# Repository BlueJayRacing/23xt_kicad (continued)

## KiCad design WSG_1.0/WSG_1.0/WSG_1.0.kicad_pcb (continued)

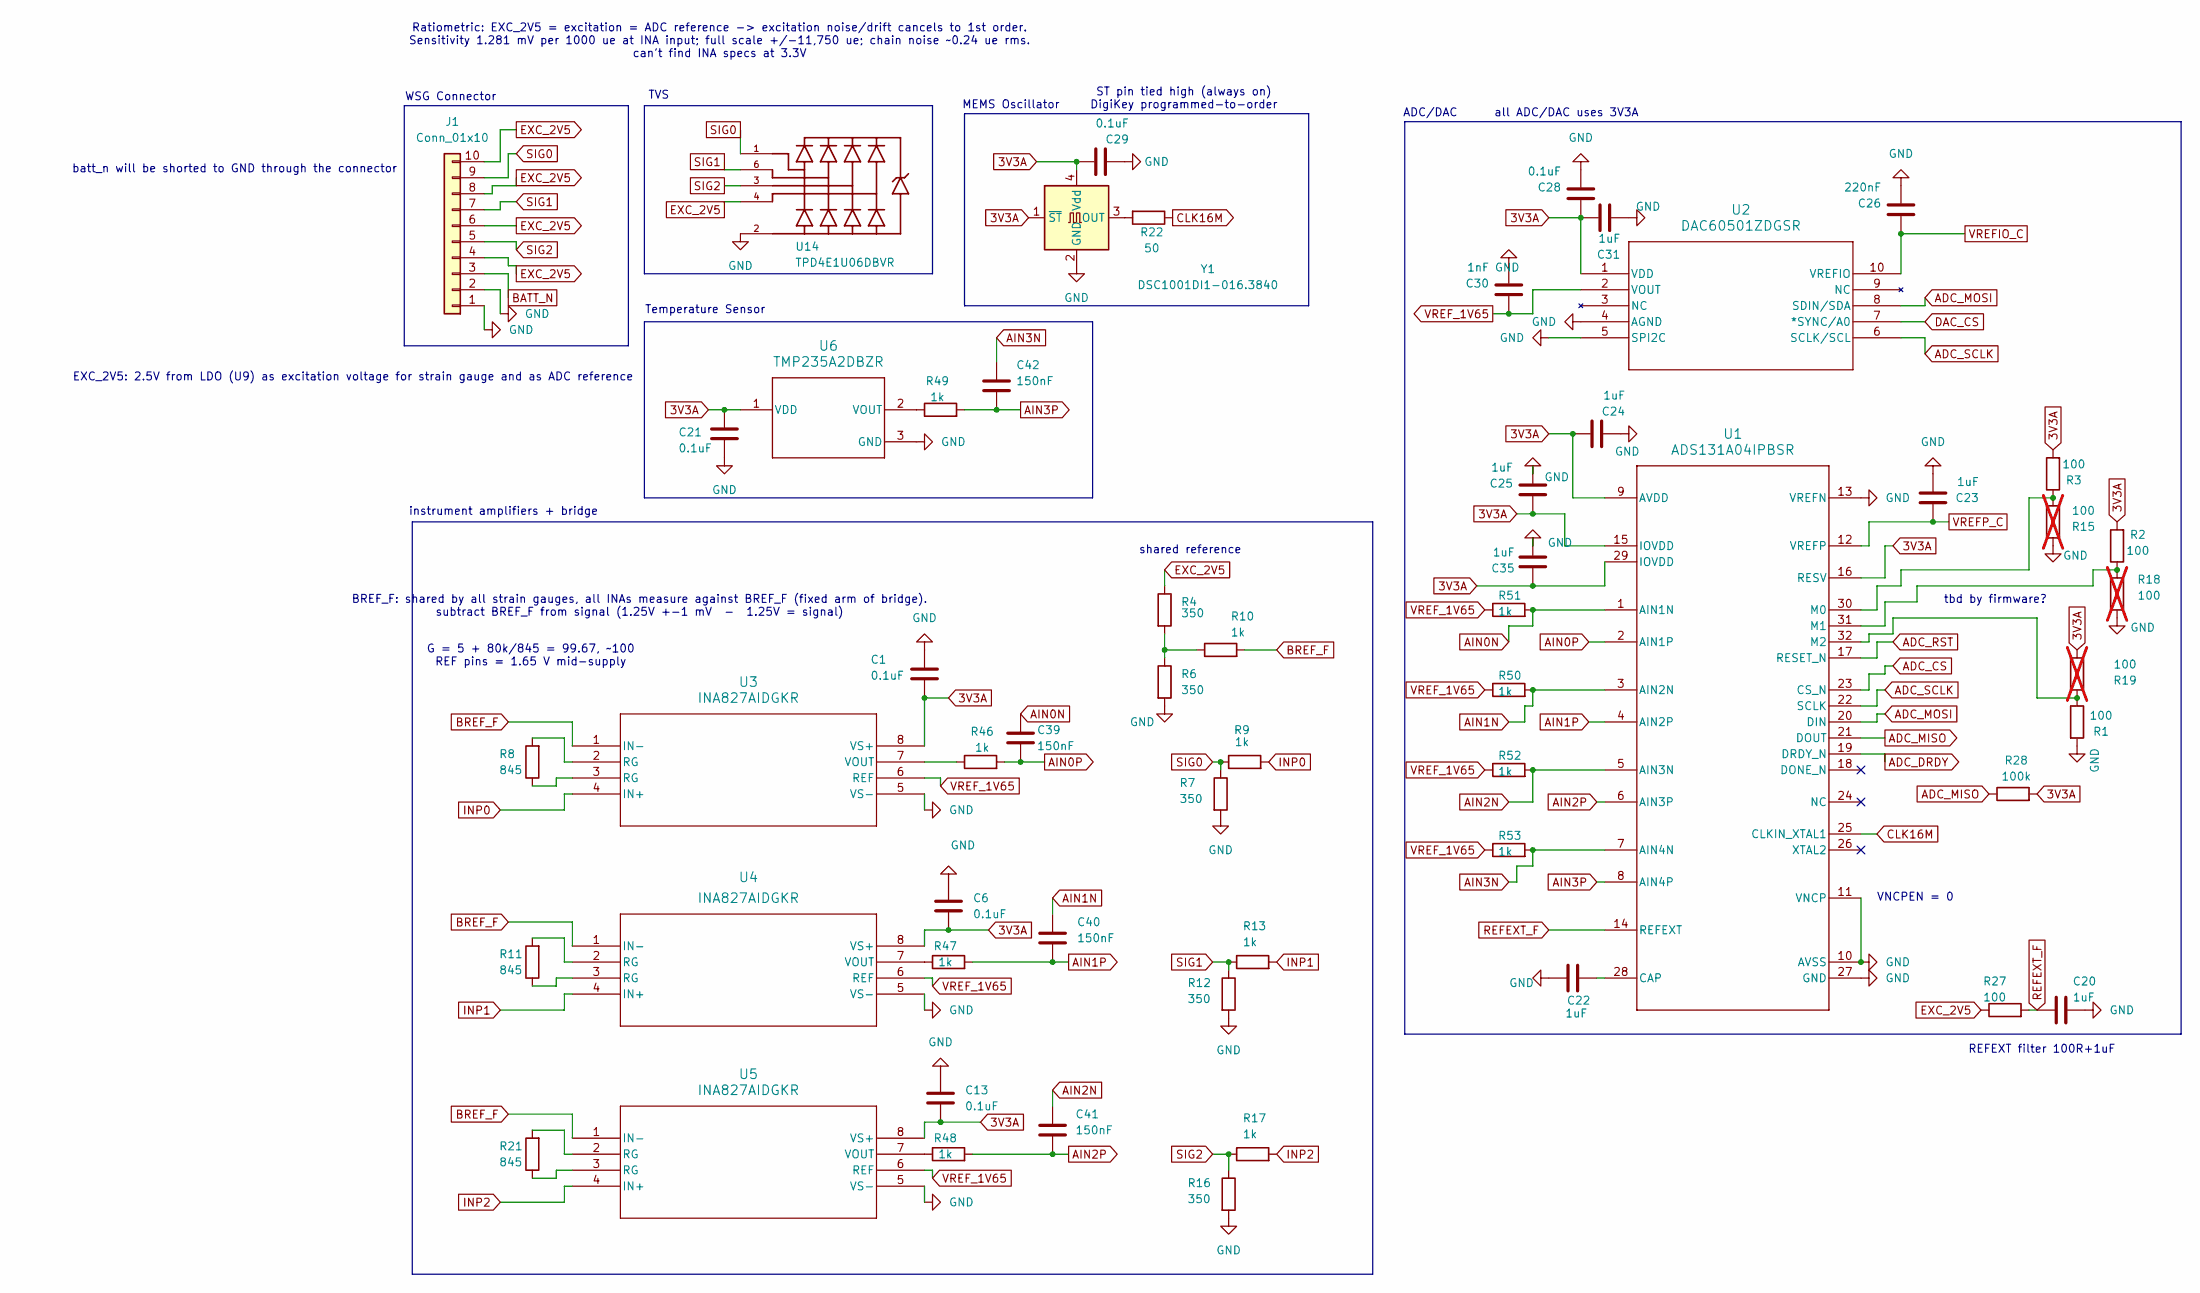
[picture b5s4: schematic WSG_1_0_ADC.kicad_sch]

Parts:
C1, C6, C13, C21, C28, C29: 0.1uF; C_0402_1005Metric_Pad0.74x0.62mm_HandSolder
C20, C22, C23, C24, C25, C31, C35: 1uF; C_0402_1005Metric_Pad0.74x0.62mm_HandSolder
C26: 220nF; C_0402_1005Metric_Pad0.74x0.62mm_HandSolder
C30: 1nF; C_0402_1005Metric_Pad0.74x0.62mm_HandSolder
C39, C40, C41, C42: 150nF; C_0402_1005Metric_Pad0.74x0.62mm_HandSolder
J1: Conn_01x10; PinHeader_2x05_P2.00mm_Vertical
R1, R2, R3, R27: 100; R_0402_1005Metric_Pad0.72x0.64mm_HandSolder
R4, R6, R7, R12, R16: 350; R_0402_1005Metric_Pad0.72x0.64mm_HandSolder
R8, R11, R21: 845; R_0402_1005Metric_Pad0.72x0.64mm_HandSolder
R9, R10, R13, R17, R46, R47, R48, R49, R50, R51, R52, R53: 1k; R_0402_1005Metric_Pad0.72x0.64mm_HandSolder
R15, R18, R19: 100; R_0402_1005Metric_Pad0.72x0.64mm_HandSolder; not fitted
R22: 50; R_0402_1005Metric_Pad0.72x0.64mm_HandSolder
R28: 100k; R_0402_1005Metric_Pad0.72x0.64mm_HandSolder
U1: ADS131A04IPBSR; TQFP-32_5x5mm_P0.5mm
U2: DAC60501ZDGSR; MSOP-10_3x3mm_P0.5mm
U3, U4, U5: INA827AIDGKR; VSSOP-8_3x3mm_P0.65mm
U6: TMP235A2DBZR; SOT-23
U14: TPD4E1U06DBVR; SOT95P280X145-6N; PARTREV D
Y1: DSC1001DI1-016.3840; Oscillator_SMD_SiT_PQFN-4Pin_2.5x2.0mm

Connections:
3V3A: C1.1, C6.1, C13.1, C21.1, C24.2, C25.2, C28.2, C29.2, C31.2, C35.2, R2.2, R3.2, R19.1, R28.2, U1.9 (AVDD), U1.15 (IOVDD), U1.16 (RESV), U1.29 (IOVDD), U2.1 (VDD), U3.8 (VS+), U4.8 (VS+), U5.8 (VS+), U6.1 (VDD), Y1.1 (~ST), Y1.4 (Vdd); also elsewhere on the board
ADC_CS: U1.23 (CS_N); also elsewhere on the board
ADC_DRDY: U1.19 (DRDY_N); also elsewhere on the board
ADC_MISO: R28.1, U1.21 (DOUT); also elsewhere on the board
ADC_MOSI: U1.20 (DIN), U2.8 (SDIN/SDA); also elsewhere on the board
ADC_RST: U1.17 (RESET_N); also elsewhere on the board
ADC_SCLK: U1.22 (SCLK), U2.6 (SCLK/SCL); also elsewhere on the board
AIN0N: C39.2, R51.2, U1.1 (AIN1N)
AIN0P: C39.1, R46.2, U1.2 (AIN1P)
AIN1N: C40.2, R50.2, U1.3 (AIN2N)
AIN1P: C40.1, R47.2, U1.4 (AIN2P)
AIN2N: C41.2, R52.2, U1.5 (AIN3N)
AIN2P: C41.1, R48.2, U1.6 (AIN3P)
AIN3N: C42.2, R53.2, U1.7 (AIN4N)
AIN3P: C42.1, R49.2, U1.8 (AIN4P)
BATT_N: J1.3; also elsewhere on the board
BREF_F: R10.2, U3.1 (IN-), U4.1 (IN-), U5.1 (IN-)
CLK16M: R22.1, U1.25 (CLKIN_XTAL1)
DAC_CS: U2.7 (*SYNC/A0); also elsewhere on the board
EXC_2V5: J1.4, J1.6, J1.8, J1.10, R4.1, R27.1, U14.4; also elsewhere on the board
GND: C1.2, C6.2, C13.2, C20.2, C21.2, C22.1, C23.1, C24.1, C25.1, C26.1, C28.1, C29.1, C30.1, C31.1, C35.1, J1.1, J1.2, R1.2, R6.2, R7.2, R12.2, R15.1, R16.2, R18.1, U1.10 (AVSS), U1.11 (VNCP), U1.13 (VREFN), U1.27 (GND), U2.4 (AGND), U2.5 (SPI2C), U3.5 (VS-), U4.5 (VS-), U5.5 (VS-), U6.3 (GND), U14.2, Y1.2 (GND); also elsewhere on the board
INP0: R9.2, U3.4 (IN+)
INP1: R13.2, U4.4 (IN+)
INP2: R17.2, U5.4 (IN+)
unnamed: R8.1, U3.3 (RG)
unnamed: R8.2, U3.2 (RG)
unnamed: R4.2, R6.1, R10.1
unnamed: R11.1, U4.3 (RG)
unnamed: R11.2, U4.2 (RG)
unnamed: R21.1, U5.3 (RG)
unnamed: R21.2, U5.2 (RG)
unnamed: C22.2, U1.28 (CAP)
unnamed: R3.1, R15.2, U1.30 (M0)
unnamed: R2.1, R18.2, U1.31 (M1)
unnamed: R1.1, R19.2, U1.32 (M2)
unnamed: R46.1, U3.7 (VOUT)
unnamed: R47.1, U4.7 (VOUT)
unnamed: R48.1, U5.7 (VOUT)
unnamed: R49.1, U6.2 (VOUT)
unnamed: R22.2, Y1.3 (OUT)
REFEXT_F: C20.1, R27.2, U1.14 (REFEXT)
SIG0: J1.9, R7.1, R9.1, U14.1
SIG1: J1.7, R12.1, R13.1, U14.6
SIG2: J1.5, R16.1, R17.1, U14.3
VREFIO_C: C26.2, U2.10 (VREFIO)
VREFP_C: C23.2, U1.12 (VREFP)
VREF_1V65: C30.2, R50.1, R51.1, R52.1, R53.1, U2.2 (VOUT), U3.6 (REF), U4.6 (REF), U5.6 (REF); also elsewhere on the board

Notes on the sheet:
batt_n will be shorted to GND through the connector
Ratiometric: EXC_2V5 = excitation = ADC reference -> excitation noise/drift cancels to 1st order. Sensitivity 1.281 mV per 1000 ue at INA input; full scale +/-11,750 ue; chain noise ~0.24 ue rms. can't find INA specs at 3.3V
instrument amplifiers + bridge
BREF_F: shared by all strain gauges, all INAs measure against BREF_F (fixed arm of bridge). subtract BREF_F from signal (1.25V +-1 mV - 1.25V = signal)
shared reference
EXC_2V5: 2.5V from LDO (U9) as excitation voltage for strain gauge and as ADC reference
ADC/DAC
all ADC/DAC uses 3V3A
REFEXT filter 100R+1uF
G = 5 + 80k/845 = 99.67, ~100 REF pins = 1.65 V mid-supply
MEMS Oscillator
Temperature Sensor
WSG Connector
TVS
tbd by firmware?
VNCPEN = 0
ST pin tied high (always on) DigiKey programmed-to-order

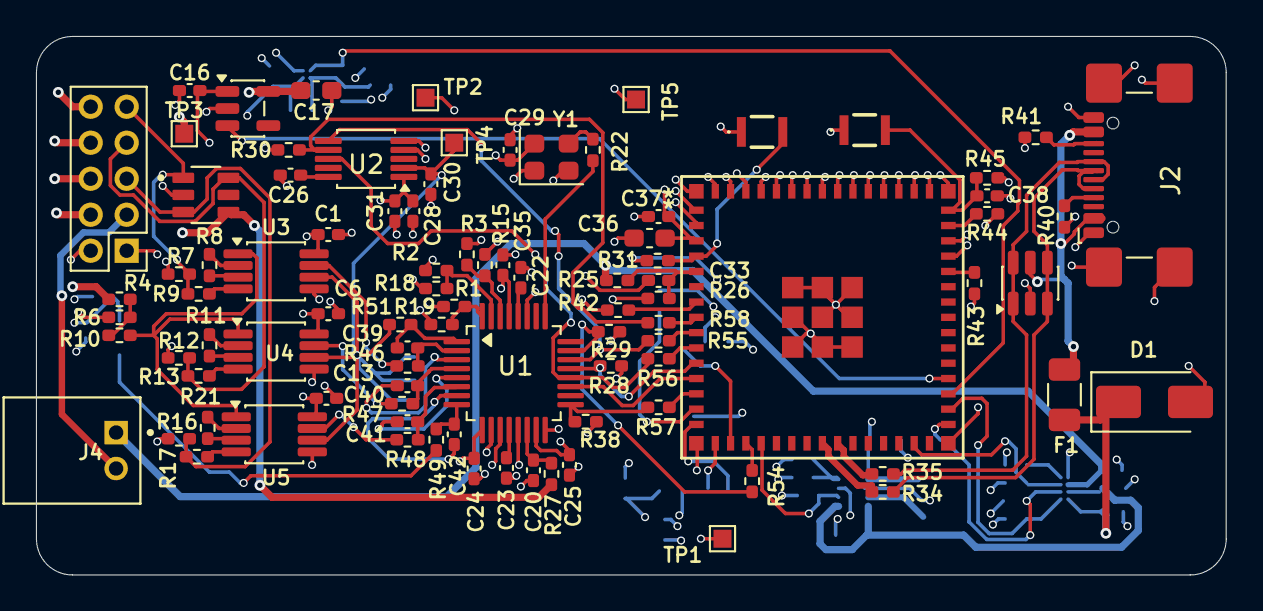
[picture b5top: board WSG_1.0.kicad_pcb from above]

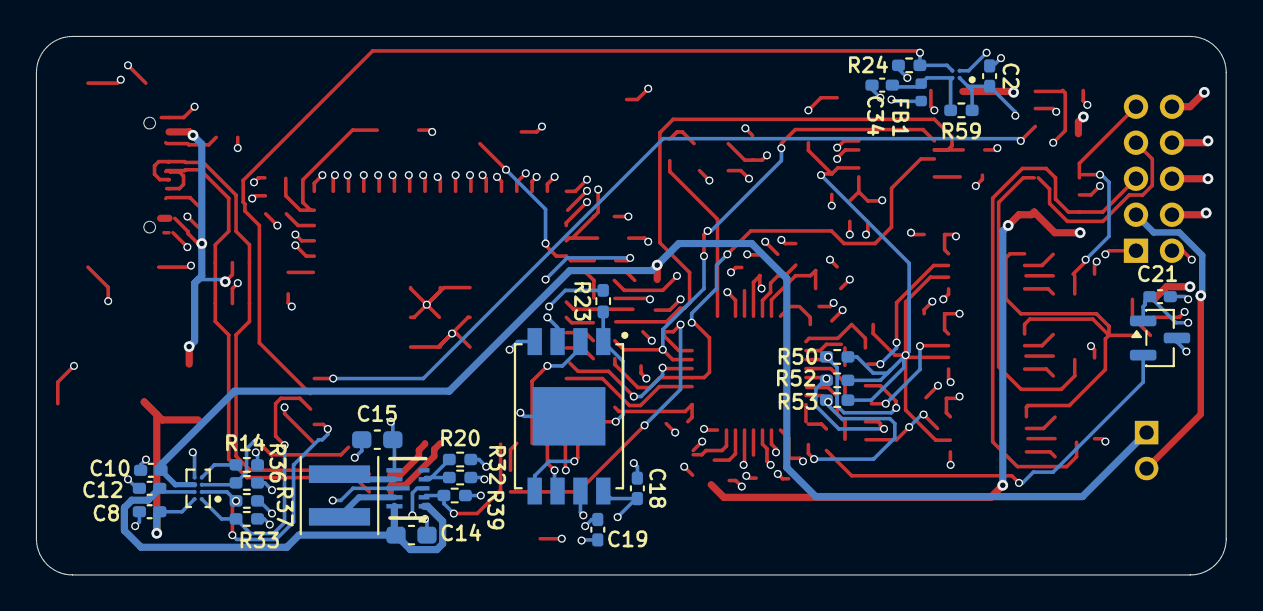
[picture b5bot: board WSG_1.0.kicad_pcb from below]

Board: 4 copper layers, 66.1 x 29.9 mm, 121 parts (30 on the bottom side), 84 nets.

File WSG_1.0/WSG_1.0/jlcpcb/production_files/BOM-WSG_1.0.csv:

Comment,Designator,Footprint,LCSC,Quantity
0.1uF,"C1,C13,C18,C21,C28,C29,C37,C6",C_0402_1005Metric_Pad0.74x0.62mm_HandSolder,C1525,8
0ZCJ0075AF2E,F1,Fuse_1206_3216Metric,C3761319,1
10.2k,R14,R_0402_1005Metric_Pad0.72x0.64mm_HandSolder,C11660,1
100,"R1,R2,R27,R3",R_0402_1005Metric_Pad0.72x0.64mm_HandSolder,C25076,4
100k,"R23,R24,R28,R29,R30,R38,R39",R_0402_1005Metric_Pad0.72x0.64mm_HandSolder,C25741,7
100nF,C33,C_0402_1005Metric_Pad0.74x0.62mm_HandSolder,C1525,1
10k,"R31,R33,R36,R37,R42,R43,R44,R45",R_0402_1005Metric_Pad0.72x0.64mm_HandSolder,C25744,8
10uF,"C10,C12",C_0402_1005Metric_Pad0.74x0.62mm_HandSolder,C15525,2
10uF,C17,C_0603_1608Metric_Pad1.08x0.95mm_HandSolder,C19702,1
150nF,"C39,C40,C41,C42",C_0402_1005Metric_Pad0.74x0.62mm_HandSolder,C162182,4
1M,"R25,R26",R_0402_1005Metric_Pad0.72x0.64mm_HandSolder,C26083,2
1k,"R10,R13,R17,R46,R47,R48,R49,R50,R51,R52,R53,R54,R55,R56,R57,R58,R9",R_0402_1005Metric_Pad0.72x0.64mm_HandSolder,C11702,17
1nF,C30,C_0402_1005Metric_Pad0.74x0.62mm_HandSolder,C1523,1
1uF,"C16,C19,C2,C20,C22,C23,C24,C25,C31,C34,C35,C38,C8",C_0402_1005Metric_Pad0.74x0.62mm_HandSolder,C52923,13
22,"R34,R35",R_0402_1005Metric_Pad0.72x0.64mm_HandSolder,C25092,2
220nF,C26,C_0402_1005Metric_Pad0.74x0.62mm_HandSolder,C16772,1
22uF,"C14,C15,C36",C_0603_1608Metric_Pad1.08x0.95mm_HandSolder,C59461,3
350,"R12,R16,R4,R6,R7",R_0402_1005Metric_Pad0.72x0.64mm_HandSolder,C852731,5
470nH,L1,L_Coilcraft_XxL4020,C5837785,1
5.1k,"R40,R41",R_0402_1005Metric_Pad0.72x0.64mm_HandSolder,C25905,2
50,R22,R_0402_1005Metric_Pad0.72x0.64mm_HandSolder,C25120,1
511k,R20,R_0402_1005Metric_Pad0.72x0.64mm_HandSolder,C64042,1
600R@100MHz,FB1,L_0402_1005Metric,C76884,1
845,"R11,R21,R8",R_0402_1005Metric_Pad0.72x0.64mm_HandSolder,C852931,3
91k,R32,R_0402_1005Metric_Pad0.72x0.64mm_HandSolder,C4147,1
ADS131A04IPBSR,U1,TQFP-32_5x5mm_P0.5mm,C2861481,1
BQ25180YBGR,U7,IC_BQ25180YBGR,C3682423,1
DAC60501ZDGSR,U2,MSOP-10_3x3mm_P0.5mm,C1852027,1
DSC1001DI1-016.3840,Y1,Oscillator_SMD_SiT_PQFN-4Pin_2.5x2.0mm,C1670360,1
ESP32-S3-MINI-1U-N8,U15,ESP32-S3-MINI-1U_EXP,C2980299,1
INA827AIDGKR,"U3,U4,U5",VSSOP-8_3x3mm_P0.65mm,C2860185,3
LP5907MFX-2.5/NOPB,U9,SOT-23-5,C165132,1
SMAJ5.0A,D1,D_SMA,C10758,1
SW_Push,"SW3,SW4",NANOT100AS_butt,C2760981,2
TMP235A2DBZR,U6,SOT-23,C2868808,1
TPD4E1U06DBVR,U14,SOT95P280X145-6N,C124691,1
TPS22916CYFPR,U10,IC_TPS22916BYFPR,C2680319,1
TPS63802DLAR,U8,DLA0010A,C2845237,1
USBLC6-2SC6,U12,SOT-23-6,C7519,1
USB_C_Receptacle_USB2.0_16P,J2,USB_C_Receptacle_GCT_USB4110,C5143397,1
W25N04KVZEIR,U11,IC_W25N04KVZEIR,C5342170,1
Conn_01x10,J1,PinHeader_2x05_P2.00mm_Vertical,,1
Conn_01x02,J4,JST_S2B-PH-K-S_LF__SN_-2pin_male,,1

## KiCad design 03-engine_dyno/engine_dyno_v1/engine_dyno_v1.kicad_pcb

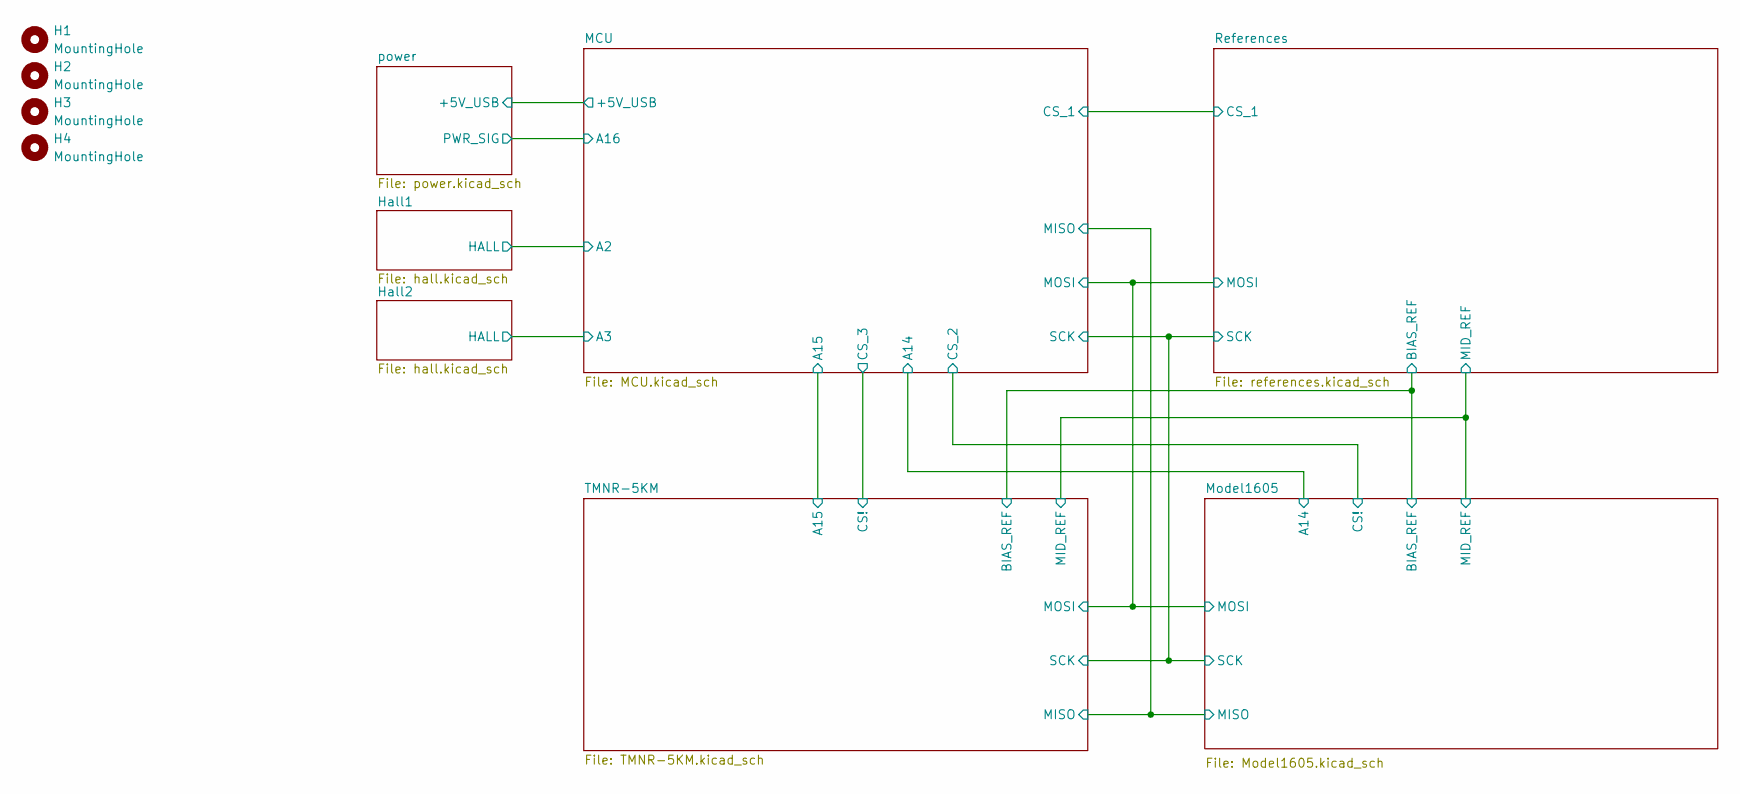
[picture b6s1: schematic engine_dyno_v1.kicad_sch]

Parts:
H1, H2, H3, H4: MountingHole; MountingHole_3.2mm_M3_DIN965_Pad

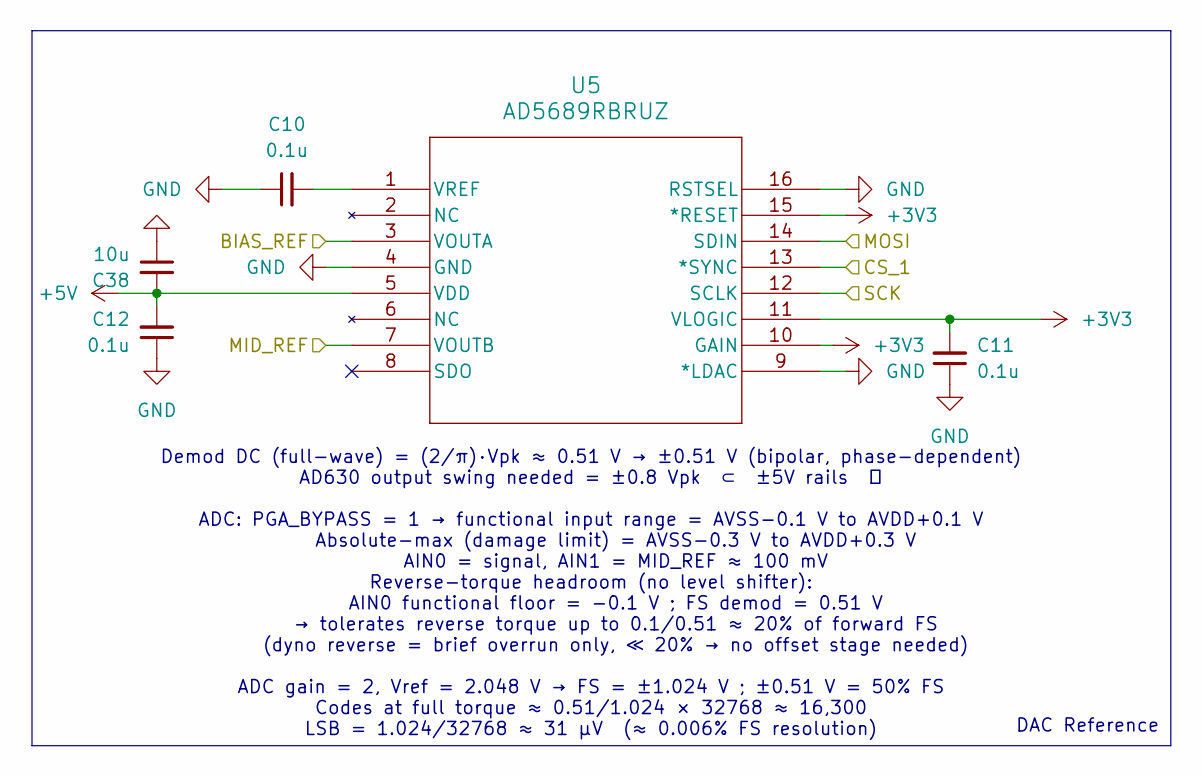
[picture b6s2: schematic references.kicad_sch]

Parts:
C10, C11, C12: 0.1u; C_0402_1005Metric
C38: 10u; C_0402_1005Metric
U5: AD5689RBRUZ; RU_16_ADI

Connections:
+3V3: C11.2, U5.10 (GAIN), U5.11 (VLOGIC), U5.15 (*RESET); also elsewhere on the board
+5V: C12.2, C38.2, U5.5 (VDD); also elsewhere on the board
/MCU/CS_1: U5.13 (*SYNC); also elsewhere on the board
/MCU/MOSI: U5.14 (SDIN); also elsewhere on the board
/MCU/SCK: U5.12 (SCLK); also elsewhere on the board
/Model1605/BIAS_REF: U5.3 (VOUTA); also elsewhere on the board
/Model1605/MID_REF: U5.7 (VOUTB); also elsewhere on the board
GND: C10.1, C11.1, C12.1, C38.1, U5.4 (GND), U5.9 (*LDAC), U5.16 (RSTSEL); also elsewhere on the board
unnamed: C10.2, U5.1 (VREF)

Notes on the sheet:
Demod DC (full-wave) = (2/π)·Vpk ≈ 0.51 V → ±0.51 V (bipolar, phase-dependent) AD630 output swing needed = ±0.8 Vpk ⊂ ±5V rails ✓ ADC: PGA_BYPASS = 1 → functional input range = AVSS−0.1 V to AVDD+0.1 V Absolute-max (damage limit) = AVSS−0.3 V to AVDD+0.3 V AIN0 = signal, AIN1 = MID_REF ≈ 100 mV Rev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
DAC Reference

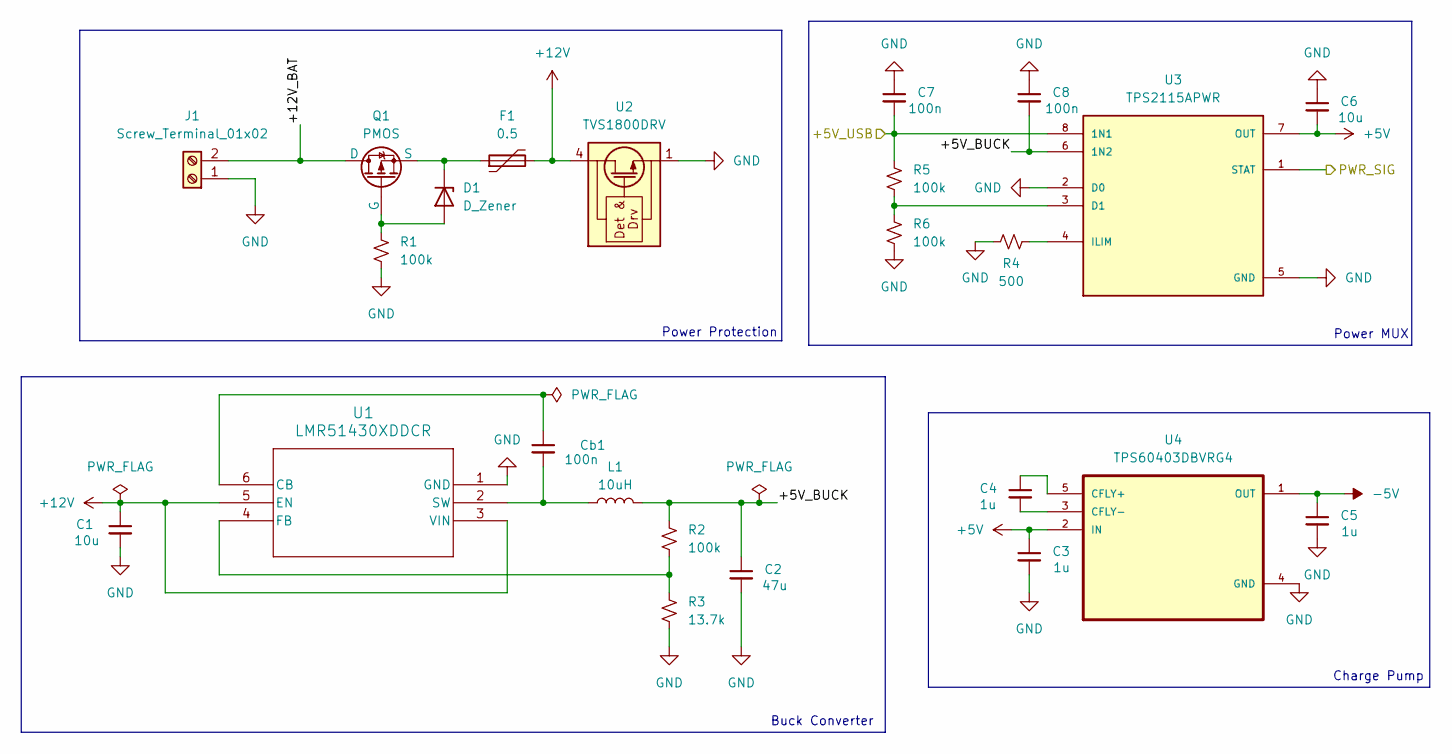
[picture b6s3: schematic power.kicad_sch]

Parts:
C1, C6: 10u; C_0402_1005Metric
C2: 47u; C_0402_1005Metric
C3, C4, C5: 1u; C_0402_1005Metric
C7, C8: 100n; C_0402_1005Metric
Cb1: 100n; C_0402_1005Metric
D1: D_Zener; D_SOD-123F
F1: 0.5; 0ZCH0050FF2G
J1: Screw_Terminal_01x02; TerminalBlock_RND_205-00232_1x02_P5.08mm_Horizontal
L1: 10uH; WE-MAPI_3020; MPN 74438336100
Q1: PMOS; SOT-23-3
R1, R2, R5, R6: 100k; R_0402_1005Metric
R3: 13.7k; R_0402_1005Metric
R4: 500; R_0402_1005Metric
U1: LMR51430XDDCR; SOT-23-THIN-6_DDC_TEX
U2: TVS1800DRV; WSON-6-1EP_2x2mm_P0.65mm_EP1x1.6mm
U3: TPS2115APWR; SOP65P640X120-8N; PARTREV F
U4: TPS60403DBVRG4; SOT95P280X145-5N

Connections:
+5V: C3.1, C6.2, U3.7 (OUT), U4.2 (IN); also elsewhere on the board
+12V: C1.1, F1.2, U1.3 (VIN), U1.5 (EN), U2.4 (IN), U2.5 (IN), U2.6 (IN)
-5V: C5.1, U4.1 (OUT); also elsewhere on the board
/MCU/+5V_USB: C7.2, R5.2, U3.8 (1N1); also elsewhere on the board
/MCU/A16: U3.1 (STAT); also elsewhere on the board
/power/+5V_BUCK: C2.1, C8.2, L1.2, R2.1, U3.6 (1N2)
/power/+12V_BAT: J1.2, Q1.1 (D)
GND: C1.2, C2.2, C3.2, C5.2, C6.1, C7.1, C8.1, J1.1, R1.2, R3.2, R4.2, R6.1, U1.1 (GND), U2.1 (GND), U2.2 (GND), U2.3 (GND), U2.7 (GND), U3.2 (D0), U3.5 (GND), U4.4 (GND); also elsewhere on the board
unnamed: D1.2 (A), Q1.2 (G), R1.1
unnamed: D1.1 (K), F1.1, Q1.3 (S)
unnamed: Cb1.1, U1.6 (CB)
unnamed: R2.2, R3.1, U1.4 (FB)
unnamed: Cb1.2, L1.1, U1.2 (SW)
unnamed: R5.1, R6.2, U3.3 (D1)
unnamed: R4.1, U3.4 (ILIM)
unnamed: C4.1, U4.5 (CFLY+)
unnamed: C4.2, U4.3 (CFLY-)

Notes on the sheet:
Power MUX
Charge Pump
Buck Converter
Power Protection

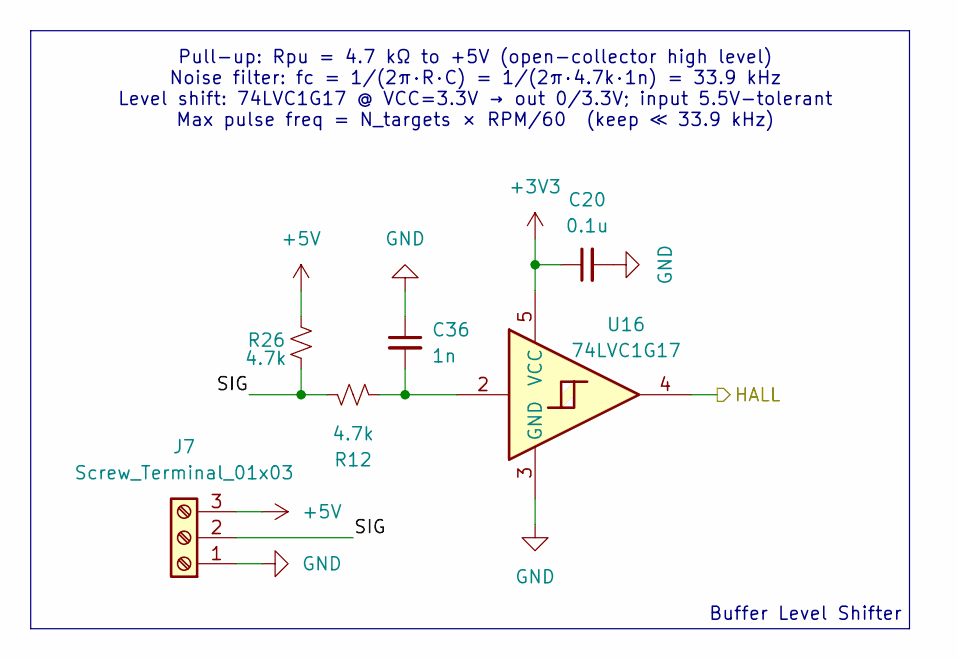
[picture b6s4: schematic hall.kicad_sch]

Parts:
C20: 0.1u; C_0402_1005Metric
C36: 1n; C_0402_1005Metric
J7: Screw_Terminal_01x03; TerminalBlock_RND_205-00233_1x03_P5.08mm_Horizontal
R12, R26: 4.7k; R_0402_1005Metric
U16: 74LVC1G17; SOT-23-5

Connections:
+3V3: C20.1, U16.5 (VCC); also elsewhere on the board
+5V: J7.3, R26.1; also elsewhere on the board
/Hall1/HALL: U16.4; also elsewhere on the board
/Hall1/SIG: J7.2, R12.1, R26.2
GND: C20.2, C36.1, J7.1, U16.3 (GND); also elsewhere on the board
unnamed: C36.2, R12.2, U16.2

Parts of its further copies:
C25: 0.1u; C_0402_1005Metric
C26: 1n; C_0402_1005Metric
J5: Screw_Terminal_01x03; TerminalBlock_RND_205-00233_1x03_P5.08mm_Horizontal
R17, R18: 4.7k; R_0402_1005Metric
U11: 74LVC1G17; SOT-23-5

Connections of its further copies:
+3V3: C25.1, U11.5 (VCC); also elsewhere on the board
+5V: J5.3, R17.1; also elsewhere on the board
/Hall2/HALL: U11.4; also elsewhere on the board
/Hall2/SIG: J5.2, R17.2, R18.1
GND: C25.2, C26.1, J5.1, U11.3 (GND); also elsewhere on the board
unnamed: C26.2, R18.2, U11.2

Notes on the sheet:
Pull-up: Rpu = 4.7 kΩ to +5V (open-collector high level) Noise filter: fc = 1/(2π·R·C) = 1/(2π·4.7k·1n) = 33.9 kHz Level shift: 74LVC1G17 @ VCC=3.3V → out 0/3.3V; input 5.5V-tolerant Max pulse freq = N_targets × RPM/60 (keep ≪ 33.9 kHz)
Buffer Level Shifter

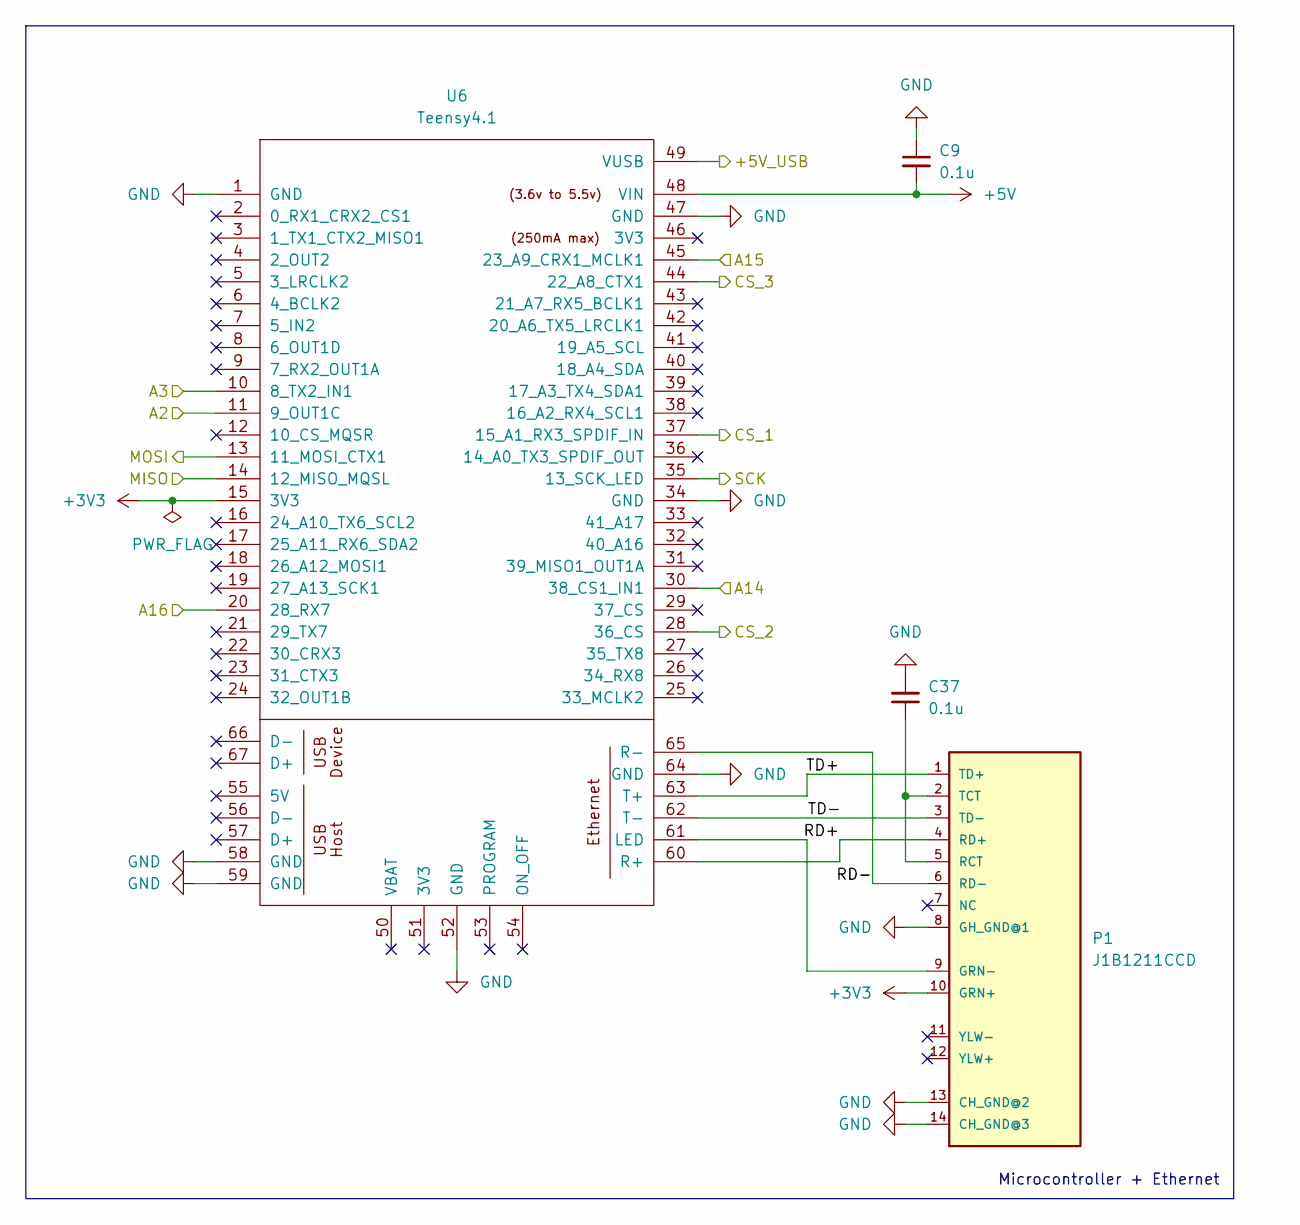
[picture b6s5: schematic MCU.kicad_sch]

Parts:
C9, C37: 0.1u; C_0402_1005Metric
P1: J1B1211CCD
U6: Teensy4.1; Teensy41

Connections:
+3V3: P1.10 (GRN+), U6.15 (3V3); also elsewhere on the board
+5V: C9.2, U6.48 (VIN); also elsewhere on the board
/Hall1/HALL: U6.11 (9_OUT1C); also elsewhere on the board
/Hall2/HALL: U6.10 (8_TX2_IN1); also elsewhere on the board
/MCU/+5V_USB: U6.49 (VUSB); also elsewhere on the board
/MCU/A14: U6.30 (38_CS1_IN1); also elsewhere on the board
/MCU/A15: U6.45 (23_A9_CRX1_MCLK1); also elsewhere on the board
/MCU/A16: U6.20 (28_RX7); also elsewhere on the board
/MCU/CS_1: U6.37 (15_A1_RX3_SPDIF_IN); also elsewhere on the board
/MCU/CS_2: U6.28 (36_CS); also elsewhere on the board
/MCU/CS_3: U6.44 (22_A8_CTX1); also elsewhere on the board
/MCU/MISO: U6.14 (12_MISO_MQSL); also elsewhere on the board
/MCU/MOSI: U6.13 (11_MOSI_CTX1); also elsewhere on the board
/MCU/RD+: P1.4 (RD+), U6.60 (R+)
/MCU/RD-: P1.6 (RD-), U6.65 (R-)
/MCU/SCK: U6.35 (13_SCK_LED); also elsewhere on the board
/MCU/TD+: P1.1 (TD+), U6.63 (T+)
/MCU/TD-: P1.3 (TD-), U6.62 (T-)
GND: C9.1, C37.2, P1.8 (GH_GND@1), P1.13 (CH_GND@2), P1.14 (CH_GND@3), U6.1 (GND), U6.34 (GND), U6.47 (GND), U6.52 (GND), U6.58 (GND), U6.59 (GND), U6.64 (GND); also elsewhere on the board
unnamed: P1.9 (GRN-), U6.61 (LED)
unnamed: C37.1, P1.2 (TCT), P1.5 (RCT)

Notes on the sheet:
Microcontroller + Ethernet

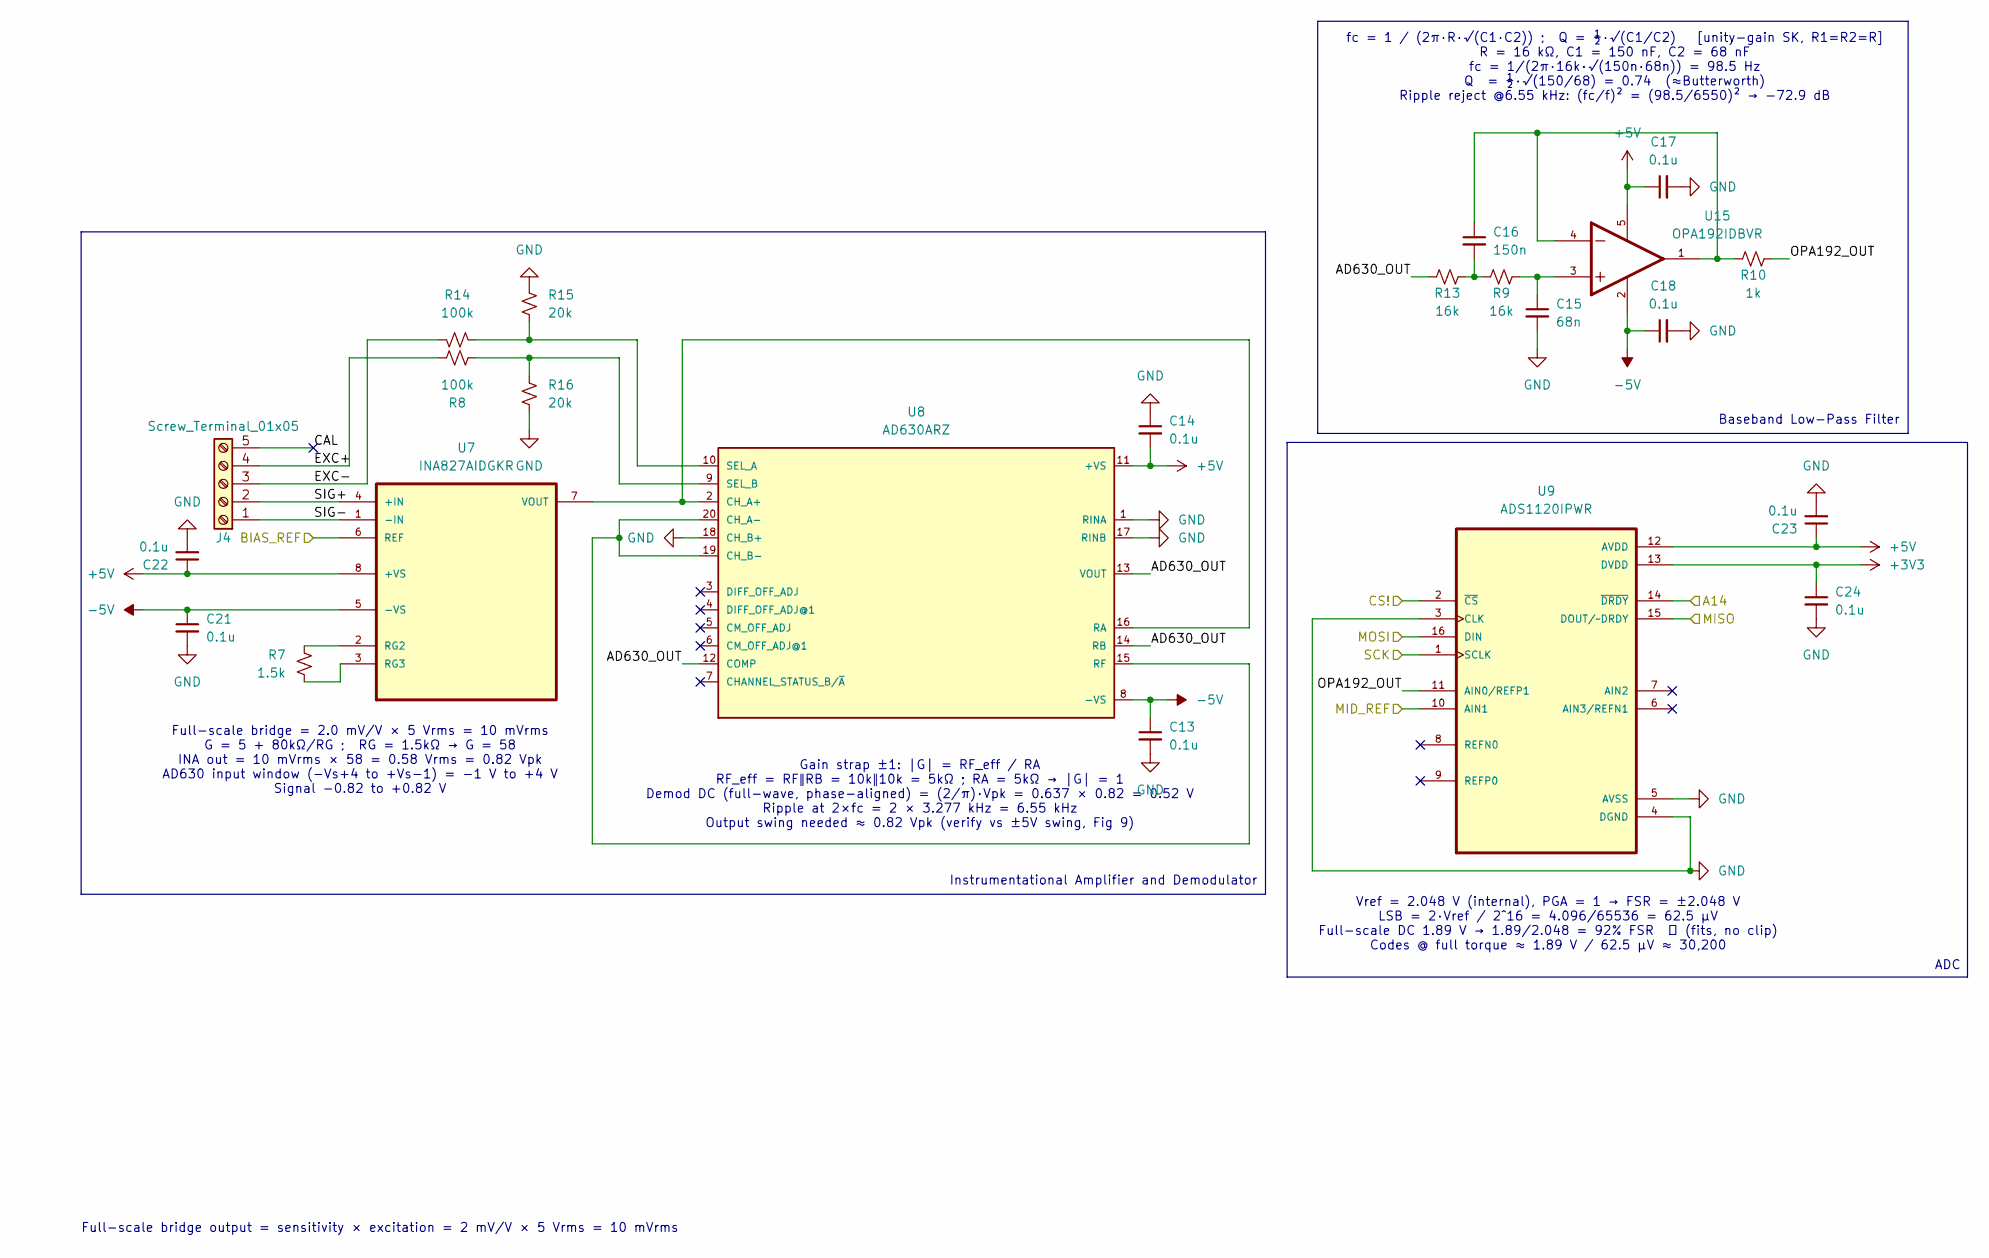
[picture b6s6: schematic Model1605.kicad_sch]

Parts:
C13, C14, C17, C18, C21, C22, C23, C24: 0.1u; C_0402_1005Metric
C15: 68n; C_0402_1005Metric
C16: 150n; C_0402_1005Metric
J4: Screw_Terminal_01x05; TerminalBlock_RND_205-00235_1x05_P5.08mm_Horizontal
R7: 1.5k; R_0402_1005Metric
R8, R14: 100k; R_0402_1005Metric
R9, R13: 16k; R_0402_1005Metric
R10: 1k; R_0402_1005Metric
R15, R16: 20k; R_0402_1005Metric
U7: INA827AIDGKR; SOP65P490X110-8N; DigiKey_Part_Number 296-30588-1-ND
U8: AD630ARZ; SOIC127P1032X265-20N
U9: ADS1120IPWR; SOP65P640X120-16N
U15: OPA192IDBVR; SOT95P280X145-5N; PARTREV F

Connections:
+3V3: C24.1, U9.13 (DVDD); also elsewhere on the board
+5V: C14.2, C17.1, C22.1, C23.1, U7.8 (+VS), U8.11 (+VS), U9.12 (AVDD), U15.5; also elsewhere on the board
-5V: C13.1, C18.1, C21.1, U7.5 (-VS), U8.8 (-VS), U15.2; also elsewhere on the board
/MCU/A14: U9.14 (~DRDY); also elsewhere on the board
/MCU/CS_2: U9.2 (~CS); also elsewhere on the board
/MCU/MISO: U9.15 (DOUT/~DRDY); also elsewhere on the board
/MCU/MOSI: U9.16 (DIN); also elsewhere on the board
/MCU/SCK: U9.1 (SCLK); also elsewhere on the board
/Model1605/AD630_OUT: R13.1, U8.12 (COMP), U8.13 (VOUT), U8.14 (RB)
/Model1605/BIAS_REF: U7.6 (REF); also elsewhere on the board
/Model1605/CAL: J4.5
/Model1605/EXC+: J4.4, R8.1
/Model1605/EXC-: J4.3, R14.1
/Model1605/MID_REF: U9.10 (AIN1); also elsewhere on the board
/Model1605/OPA192_OUT: R10.2, U9.11 (AIN0/REFP1)
/Model1605/SIG+: J4.2, U7.4 (+IN)
/Model1605/SIG-: J4.1, U7.1 (-IN)
GND: C13.2, C14.1, C15.2, C17.2, C18.2, C21.2, C22.2, C23.2, C24.2, R15.2, R16.1, U8.1 (RINA), U8.17 (RINB), U8.18 (CH_B+), U9.3 (CLK), U9.4 (DGND), U9.5 (AVSS); also elsewhere on the board
unnamed: C15.1, R9.2, U15.3
unnamed: C16.1, R10.1, U15.1, U15.4
unnamed: C16.2, R9.1, R13.2
unnamed: R7.1, U7.2 (RG2)
unnamed: R7.2, U7.3 (RG3)
unnamed: U7.7 (VOUT), U8.2 (CH_A+), U8.16 (RA)
unnamed: U8.15 (RF), U8.19 (CH_B-), U8.20 (CH_A-)
unnamed: R14.2, R15.1, U8.10 (SEL_A)
unnamed: R8.2, R16.2, U8.9 (SEL_B)

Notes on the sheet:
Baseband Low-Pass Filter
Vref = 2.048 V (internal), PGA = 1 → FSR = ±2.048 V LSB = 2·Vref / 2^16 = 4.096/65536 = 62.5 µV Full-scale DC 1.89 V → 1.89/2.048 = 92% FSR ✓ (fits, no clip) Codes @ full torque ≈ 1.89 V / 62.5 µV ≈ 30,200
Full-scale bridge = 2.0 mV/V × 5 Vrms = 10 mVrms G = 5 + 80kΩ/RG ; RG = 1.5kΩ → G = 58 INA out = 10 mVrms × 58 = 0.58 Vrms = 0.82 Vpk AD630 input window (−Vs+4 to +Vs−1) = −1 V to +4 V Signal −0.82 to +0.82 V
Full-scale bridge output = sensitivity × excitation = 2 mV/V × 5 Vrms = 10 mVrms
fc = 1 / (2π·R·√(C1·C2)) ; Q = ½·√(C1/C2) [unity-gain SK, R1=R2=R] R = 16 kΩ, C1 = 150 nF, C2 = 68 nF fc = 1/(2π·16k·√(150n·68n)) = 98.5 Hz Q = ½·√(150/68) = 0.74 (≈Butterworth) Ripple reject @6.55 kHz: (fc/f)² = (98.5/6550)² → −72.9 dB
Instrumentational Amplifier and Demodulator
ADC
Gain strap ±1: |G| = RF_eff / RA RF_eff = RF‖RB = 10k‖10k = 5kΩ ; RA = 5kΩ → |G| = 1 Demod DC (full-wave, phase-aligned) = (2/π)·Vpk = 0.637 × 0.82 = 0.52 V Ripple at 2×fc = 2 × 3.277 kHz = 6.55 kHz Output swing needed ≈ 0.82 Vpk (verify vs ±5V swing, Fig 9)
